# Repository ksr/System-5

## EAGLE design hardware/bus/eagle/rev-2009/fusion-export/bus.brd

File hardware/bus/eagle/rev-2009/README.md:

# Bus backplane, 2009 (from Eagle's backups)

Copied 2026-10-26 from `~/Documents/Projects/elf-2/ksrcad/Bus/`, where they sat beside the Rev A/B/C folders:
`eagle-backups/bus.b##` (board) and `bus.s##` (schematic), both dated 2009-02-04, Eagle 4 binary.
`bus.brd` and `bus.sch` are byte-identical copies under the names Eagle and Fusion open.

Exported from Fusion 2026-10-26 (`fusion-export/`) and converted: `hardware/bus/kicad/rev-2009/` (netlist proof MATCH
36/36), redrawn in `hardware/bus/kicad/rev-2009/schematic/`.

What the board is: **six 36-pin slots** (`C36A`), every pin bussed, 8 mounting holes, and X1, a 2-pin power connector.
Slot pins 1-30 are the System-5 bus pin for pin (pin 1 = +5V, named `5V` here; 30 = GND); 31-33 = -EF1, -EF2, -EF3
(silkscreened above the 30); 34-36 = -INP, -OUT, EXP (below). A 30-pin card fits the middle 30.
Against the 2005 Rev B board (`../rev-b/fab/bus-rev-b-silkscreen.png`): the same six 36-pin slots, but pin 36 is EXP
(Rev B: -IOM) and there is no regulator, LED or capacitors.
**X1 on the copper** (DRC of the conversion, 2026-10-26): the GND track runs down the board edge and ends on X1's pad 2, so X1 pin 2 IS GND (Eagle's netlist never logged it: the track was drawn onto the pad, not connected); both +5V branches dangle (a 75 mm run down the edge and a 7 mm stub ending about 9.5 mm from X1): X1 pin 1 is connected to nothing. X1 was evidently moved after routing. So X1 brings in GND only; +5V needs a wire from X1 pin 1 to the 5V track (slot pin 1) or comes in through a slot. To confirm with a meter: X1.2 to slot pin 30 beeps, X1.1 to slot pin 1 does not.
Photos of two bare boards (both sides): `photos/2026-10-26-*.jpg`. (The other names in the binary file, U4, DTPA, DN0..., are schematic leftovers, not parts on the board.)

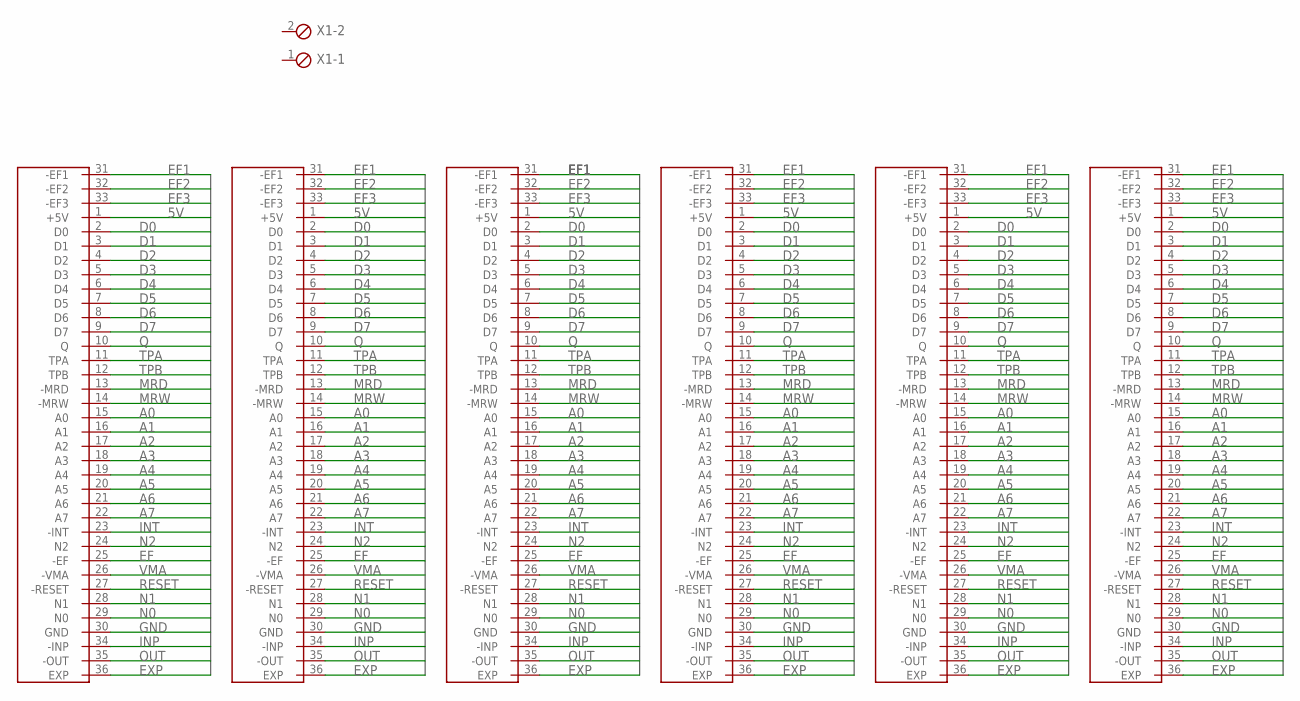
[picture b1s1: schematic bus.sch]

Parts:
U$1, U$2, U$3, U$4, U$5, U$6: C36A
X1: MPT2; 2POL254

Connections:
5V: U$1.1 (+5V), U$2.1 (+5V), U$3.1 (+5V), U$4.1 (+5V), U$5.1 (+5V), U$6.1 (+5V)
A0: U$1.15 (A0), U$2.15 (A0), U$3.15 (A0), U$4.15 (A0), U$5.15 (A0), U$6.15 (A0)
A1: U$1.16 (A1), U$2.16 (A1), U$3.16 (A1), U$4.16 (A1), U$5.16 (A1), U$6.16 (A1)
A2: U$1.17 (A2), U$2.17 (A2), U$3.17 (A2), U$4.17 (A2), U$5.17 (A2), U$6.17 (A2)
A3: U$1.18 (A3), U$2.18 (A3), U$3.18 (A3), U$4.18 (A3), U$5.18 (A3), U$6.18 (A3)
A4: U$1.19 (A4), U$2.19 (A4), U$3.19 (A4), U$4.19 (A4), U$5.19 (A4), U$6.19 (A4)
A5: U$1.20 (A5), U$2.20 (A5), U$3.20 (A5), U$4.20 (A5), U$5.20 (A5), U$6.20 (A5)
A6: U$1.21 (A6), U$2.21 (A6), U$3.21 (A6), U$4.21 (A6), U$5.21 (A6), U$6.21 (A6)
A7: U$1.22 (A7), U$2.22 (A7), U$3.22 (A7), U$4.22 (A7), U$5.22 (A7), U$6.22 (A7)
D0: U$1.2 (D0), U$2.2 (D0), U$3.2 (D0), U$4.2 (D0), U$5.2 (D0), U$6.2 (D0)
D1: U$1.3 (D1), U$2.3 (D1), U$3.3 (D1), U$4.3 (D1), U$5.3 (D1), U$6.3 (D1)
D2: U$1.4 (D2), U$2.4 (D2), U$3.4 (D2), U$4.4 (D2), U$5.4 (D2), U$6.4 (D2)
D3: U$1.5 (D3), U$2.5 (D3), U$3.5 (D3), U$4.5 (D3), U$5.5 (D3), U$6.5 (D3)
D4: U$1.6 (D4), U$2.6 (D4), U$3.6 (D4), U$4.6 (D4), U$5.6 (D4), U$6.6 (D4)
D5: U$1.7 (D5), U$2.7 (D5), U$3.7 (D5), U$4.7 (D5), U$5.7 (D5), U$6.7 (D5)
D6: U$1.8 (D6), U$2.8 (D6), U$3.8 (D6), U$4.8 (D6), U$5.8 (D6), U$6.8 (D6)
D7: U$1.9 (D7), U$2.9 (D7), U$3.9 (D7), U$4.9 (D7), U$5.9 (D7), U$6.9 (D7)
EF: U$1.25 (-EF), U$2.25 (-EF), U$3.25 (-EF), U$4.25 (-EF), U$5.25 (-EF), U$6.25 (-EF)
EF1: U$1.31 (-EF1), U$2.31 (-EF1), U$3.31 (-EF1), U$4.31 (-EF1), U$5.31 (-EF1), U$6.31 (-EF1)
EF2: U$1.32 (-EF2), U$2.32 (-EF2), U$3.32 (-EF2), U$4.32 (-EF2), U$5.32 (-EF2), U$6.32 (-EF2)
EF3: U$1.33 (-EF3), U$2.33 (-EF3), U$3.33 (-EF3), U$4.33 (-EF3), U$5.33 (-EF3), U$6.33 (-EF3)
EXP: U$1.36 (EXP), U$2.36 (EXP), U$3.36 (EXP), U$4.36 (EXP), U$5.36 (EXP), U$6.36 (EXP)
GND: U$1.30 (GND), U$2.30 (GND), U$3.30 (GND), U$4.30 (GND), U$5.30 (GND), U$6.30 (GND)
INP: U$1.34 (-INP), U$2.34 (-INP), U$3.34 (-INP), U$4.34 (-INP), U$5.34 (-INP), U$6.34 (-INP)
INT: U$1.23 (-INT), U$2.23 (-INT), U$3.23 (-INT), U$4.23 (-INT), U$5.23 (-INT), U$6.23 (-INT)
MRD: U$1.13 (-MRD), U$2.13 (-MRD), U$3.13 (-MRD), U$4.13 (-MRD), U$5.13 (-MRD), U$6.13 (-MRD)
MRW: U$1.14 (-MRW), U$2.14 (-MRW), U$3.14 (-MRW), U$4.14 (-MRW), U$5.14 (-MRW), U$6.14 (-MRW)
N0: U$1.29 (N0), U$2.29 (N0), U$3.29 (N0), U$4.29 (N0), U$5.29 (N0), U$6.29 (N0)
N1: U$1.28 (N1), U$2.28 (N1), U$3.28 (N1), U$4.28 (N1), U$5.28 (N1), U$6.28 (N1)
N2: U$1.24 (N2), U$2.24 (N2), U$3.24 (N2), U$4.24 (N2), U$5.24 (N2), U$6.24 (N2)
OUT: U$1.35 (-OUT), U$2.35 (-OUT), U$3.35 (-OUT), U$4.35 (-OUT), U$5.35 (-OUT), U$6.35 (-OUT)
Q: U$1.10 (Q), U$2.10 (Q), U$3.10 (Q), U$4.10 (Q), U$5.10 (Q), U$6.10 (Q)
RESET: U$1.27 (-RESET), U$2.27 (-RESET), U$3.27 (-RESET), U$4.27 (-RESET), U$5.27 (-RESET), U$6.27 (-RESET)
TPA: U$1.11 (TPA), U$2.11 (TPA), U$3.11 (TPA), U$4.11 (TPA), U$5.11 (TPA), U$6.11 (TPA)
TPB: U$1.12 (TPB), U$2.12 (TPB), U$3.12 (TPB), U$4.12 (TPB), U$5.12 (TPB), U$6.12 (TPB)
VMA: U$1.26 (-VMA), U$2.26 (-VMA), U$3.26 (-VMA), U$4.26 (-VMA), U$5.26 (-VMA), U$6.26 (-VMA)

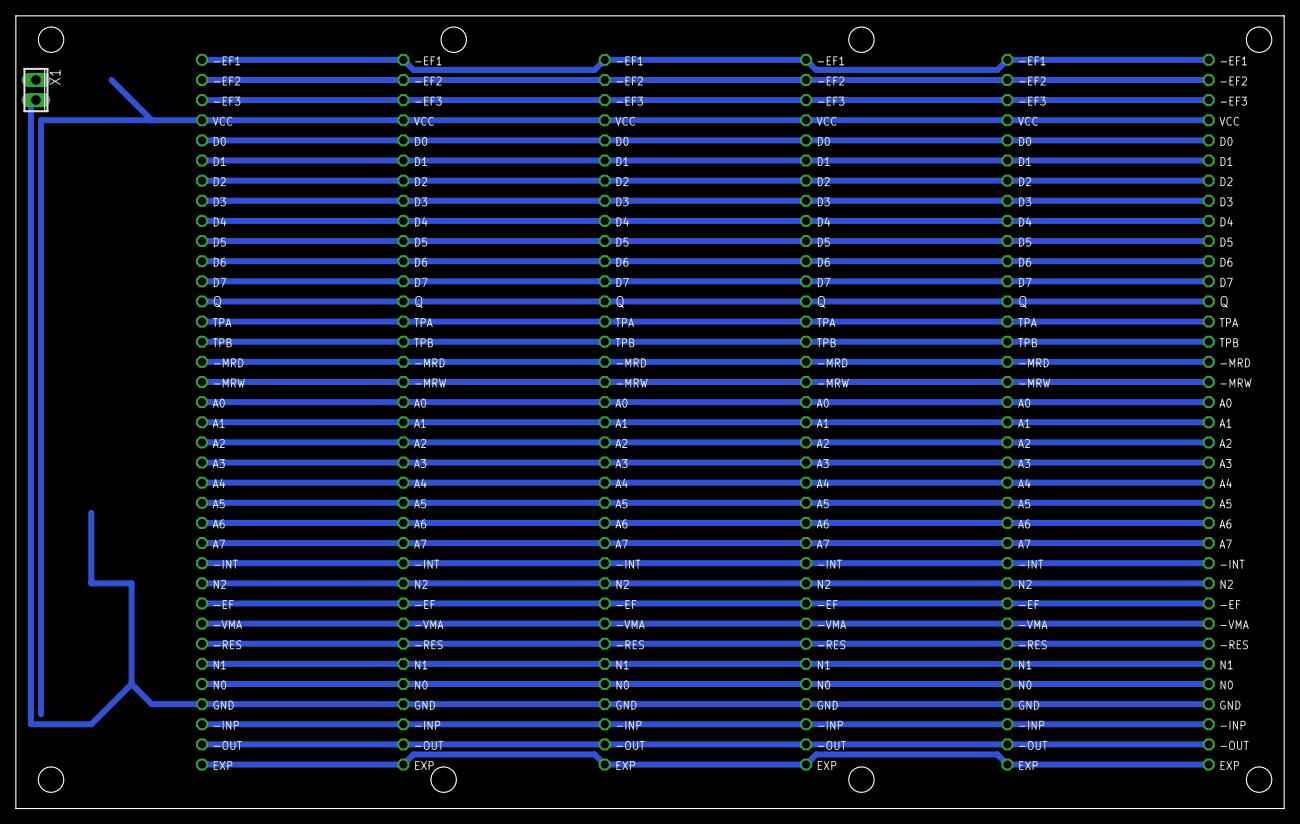
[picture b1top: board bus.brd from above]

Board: 2 copper layers, 160.0 x 100.0 mm, 7 parts (0 on the bottom side), 36 nets.

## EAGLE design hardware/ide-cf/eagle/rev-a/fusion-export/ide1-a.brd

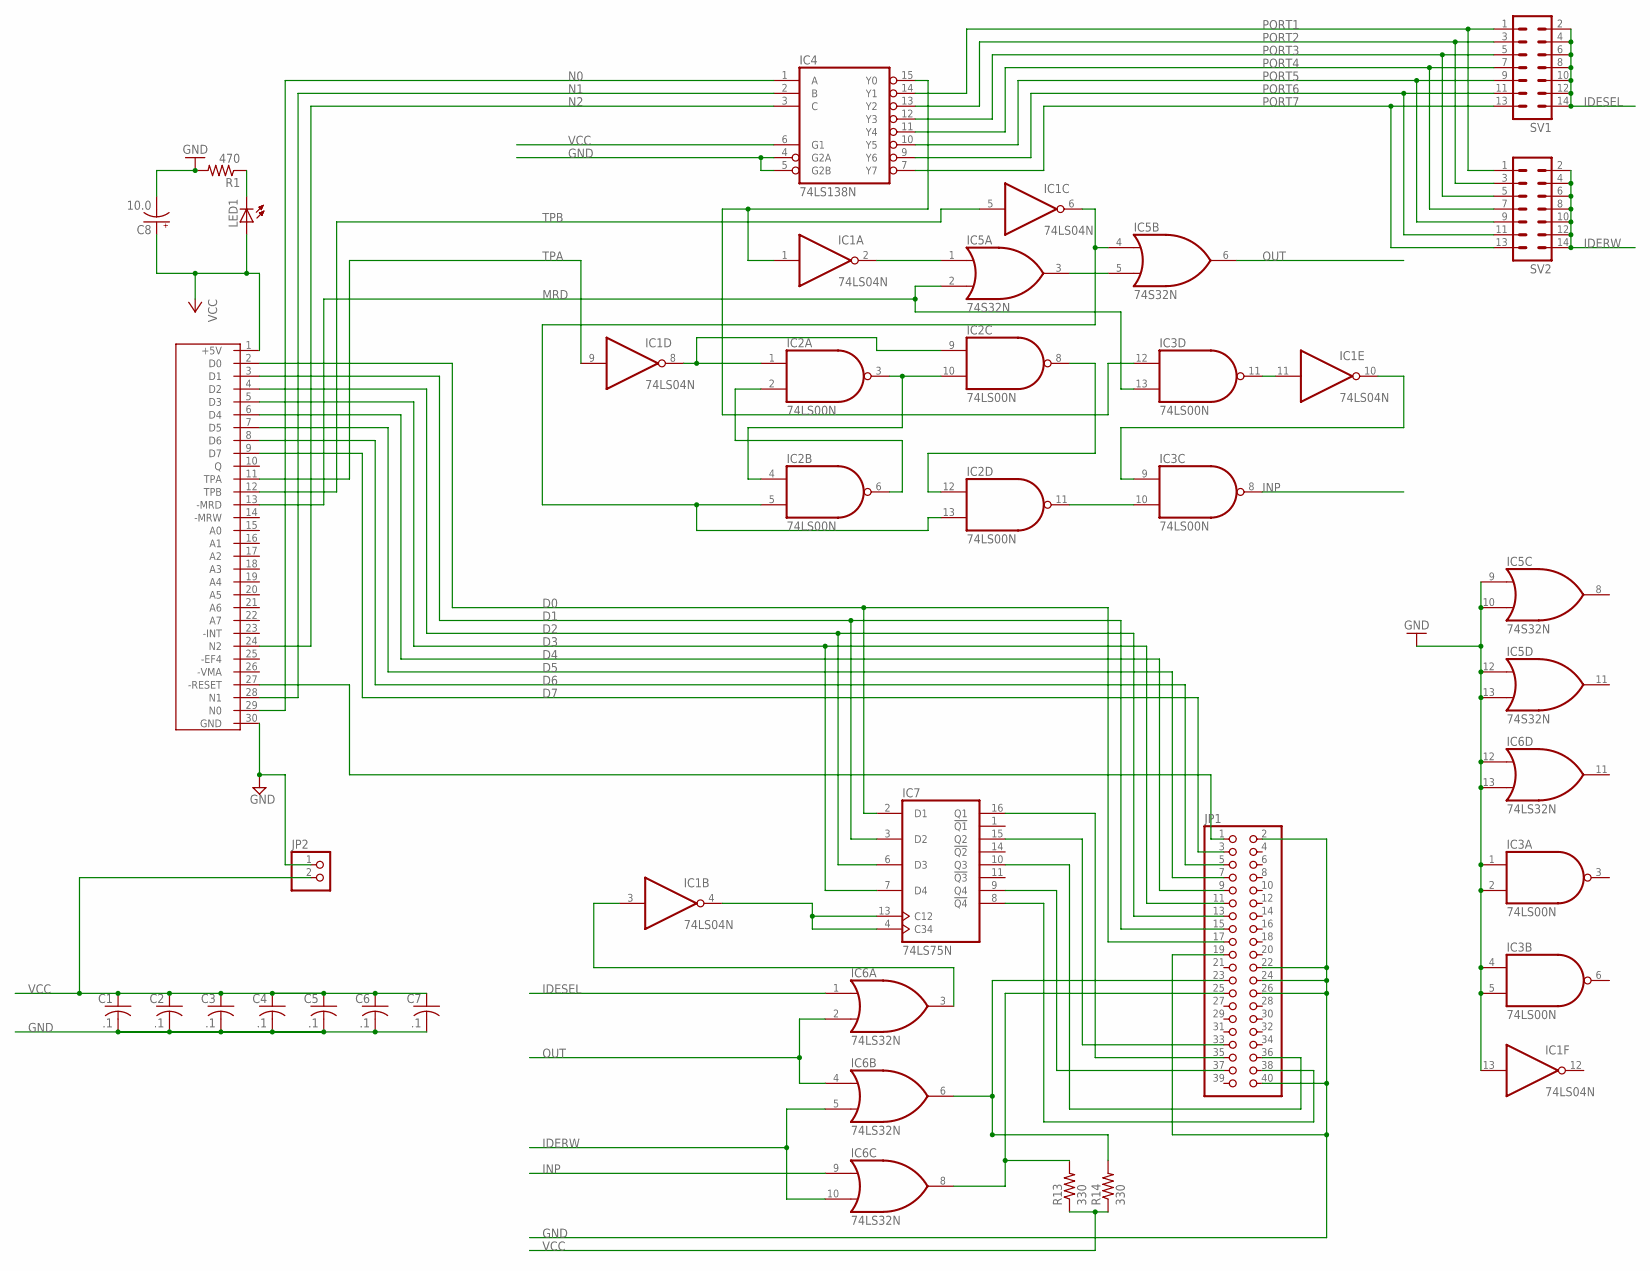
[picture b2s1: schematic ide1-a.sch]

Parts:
C1, C2, C3, C4, C5, C6, C7: .1; C025-050X050
C8: 10.0; E2,5-7
IC1: 74LS04N; DIL14
IC2, IC3: 74LS00N; DIL14
IC4: 74LS138N; DIL16
IC5: 74S32N; DIL14
IC6: 74LS32N; DIL14
IC7: 74LS75N; DIL16
JP1: PINHD-2X20; 2X20
JP2: PINHD-1X2; 1X02
LED1: LED5MM
R1: 470; 0207/7
R13, R14: 330; 0207/7
SV1, SV2: MA07-2
U$1: C30

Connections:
D0: IC7.2 (D1), JP1.17, U$1.2 (D0)
D1: IC7.3 (D2), JP1.15, U$1.3 (D1)
D2: IC7.6 (D3), JP1.13, U$1.4 (D2)
D3: IC7.7 (D4), JP1.11, U$1.5 (D3)
D4: JP1.9, U$1.6 (D4)
D5: JP1.7, U$1.7 (D5)
D6: JP1.5, U$1.8 (D6)
D7: JP1.3, U$1.9 (D7)
GND: C1.2, C2.2, C3.2, C4.2, C5.2, C6.2, C7.2, C8.-, IC1.7 (GND), IC1.13 (I), IC2.7 (GND), IC3.1 (I0), IC3.2 (I1), IC3.4 (I0), IC3.5 (I1), IC3.7 (GND), IC4.4 (G2A), IC4.5 (G2B), IC4.8 (GND), IC5.7 (GND), IC5.9 (I0), IC5.10 (I1), IC5.12 (I0), IC5.13 (I1), IC6.7 (GND), IC6.12 (I0), IC6.13 (I1), IC7.12 (GND), JP1.2, JP1.19, JP1.22, JP1.24, JP1.26, JP1.40, JP2.1, R1.2, U$1.30 (GND)
IDERW: IC6.5 (I1), IC6.10 (I1), SV2.2, SV2.4, SV2.6, SV2.8, SV2.10, SV2.12, SV2.14
IDESEL: IC6.1 (I0), SV1.2, SV1.4, SV1.6, SV1.8, SV1.10, SV1.12, SV1.14
INP: IC3.8 (O), IC6.9 (I0)
MRD: IC3.13 (I1), IC5.2 (I1), U$1.13 (-MRD)
N0: IC4.1 (A), U$1.29 (N0)
N1: IC4.2 (B), U$1.28 (N1)
N2: IC4.3 (C), U$1.24 (N2)
unnamed: IC1.1 (I), IC3.12 (I0), IC4.15 (Y0)
unnamed: IC1.2 (O), IC5.1 (I0)
unnamed: IC2.3 (O), IC2.4 (I0), IC2.10 (I1)
unnamed: IC5.3 (O), IC5.5 (I1)
unnamed: IC1.6 (O), IC2.5 (I1), IC2.13 (I1), IC5.4 (I0)
unnamed: IC2.2 (I1), IC2.6 (O)
unnamed: IC1.8 (O), IC2.1 (I0), IC2.9 (I0)
unnamed: IC1.10 (O), IC3.9 (I0)
unnamed: IC2.8 (O), IC2.12 (I0)
unnamed: IC1.3 (I), IC6.3 (O)
unnamed: IC2.11 (O), IC3.10 (I1)
unnamed: IC1.11 (I), IC3.11 (O)
unnamed: LED1.K (C), R1.1
unnamed: IC1.4 (O), IC7.4 (C34), IC7.13 (C12)
unnamed: IC7.16 (Q1), JP1.35
unnamed: IC7.15 (Q2), JP1.33
unnamed: IC7.10 (Q3), JP1.36
unnamed: IC7.9 (Q4), JP1.37
unnamed: IC7.8 (!Q4), JP1.38
unnamed: IC6.6 (O), JP1.23, R14.2
unnamed: IC6.8 (O), JP1.25, R13.2
OUT: IC5.6 (O), IC6.2 (I1), IC6.4 (I0)
PORT1: IC4.14 (Y1), SV1.1, SV2.1
PORT2: IC4.13 (Y2), SV1.3, SV2.3
PORT3: IC4.12 (Y3), SV1.5, SV2.5
PORT4: IC4.11 (Y4), SV1.7, SV2.7
PORT5: IC4.10 (Y5), SV1.9, SV2.9
PORT6: IC4.9 (Y6), SV1.11, SV2.11
PORT7: IC4.7 (Y7), SV1.13, SV2.13
RESET: JP1.1, U$1.27 (-RESET)
TPA: IC1.9 (I), U$1.11 (TPA)
TPB: IC1.5 (I), U$1.12 (TPB)
VCC: C1.1, C2.1, C3.1, C4.1, C5.1, C6.1, C7.1, C8.+, IC1.14 (VCC), IC2.14 (VCC), IC3.14 (VCC), IC4.6 (G1), IC4.16 (VCC), IC5.14 (VCC), IC6.14 (VCC), IC7.5 (VCC), JP2.2, LED1.A, R13.1, R14.1, U$1.1 (+5V)

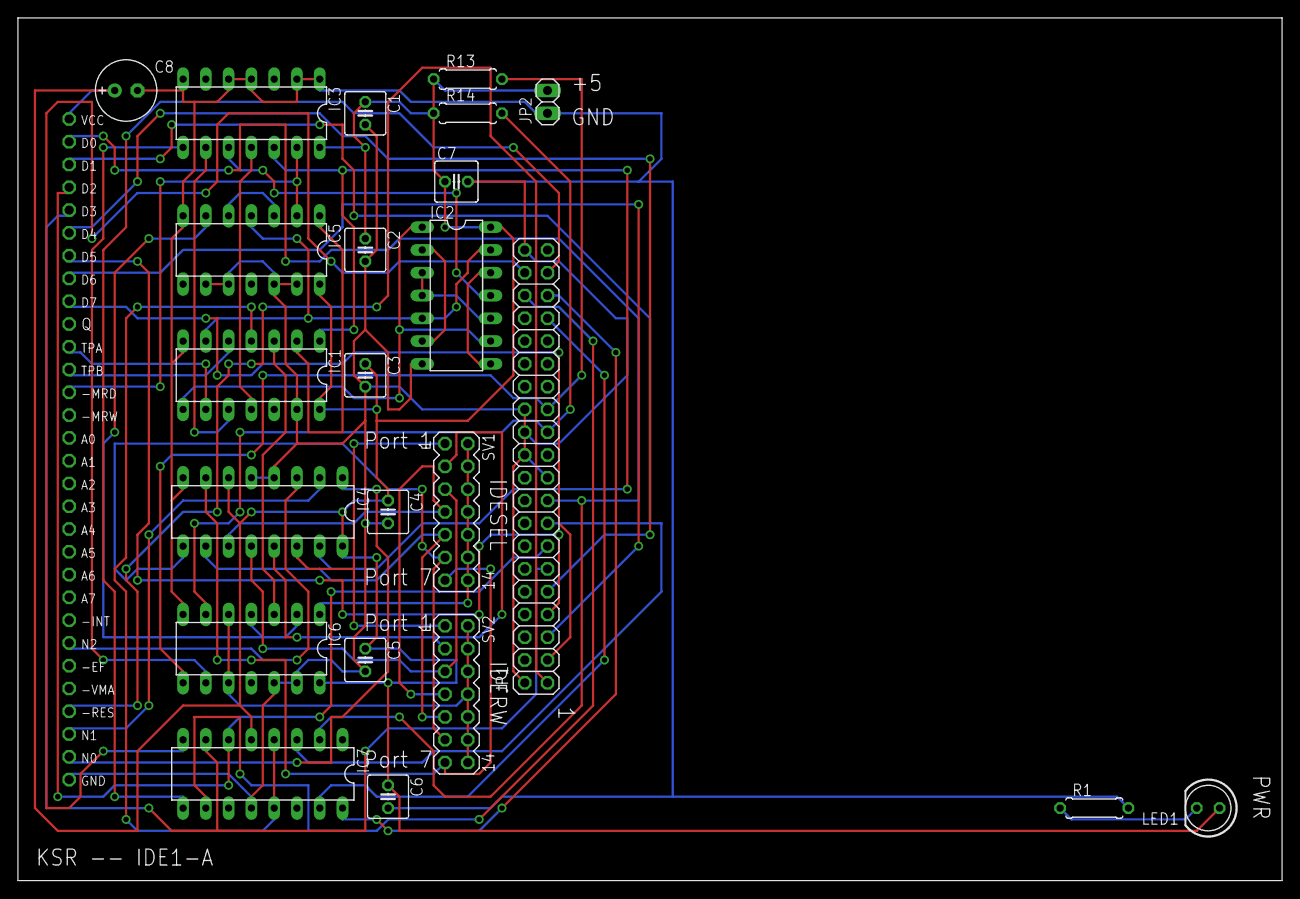
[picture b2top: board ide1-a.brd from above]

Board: 2 copper layers, 140.9 x 96.2 mm, 24 parts (0 on the bottom side), 49 nets.

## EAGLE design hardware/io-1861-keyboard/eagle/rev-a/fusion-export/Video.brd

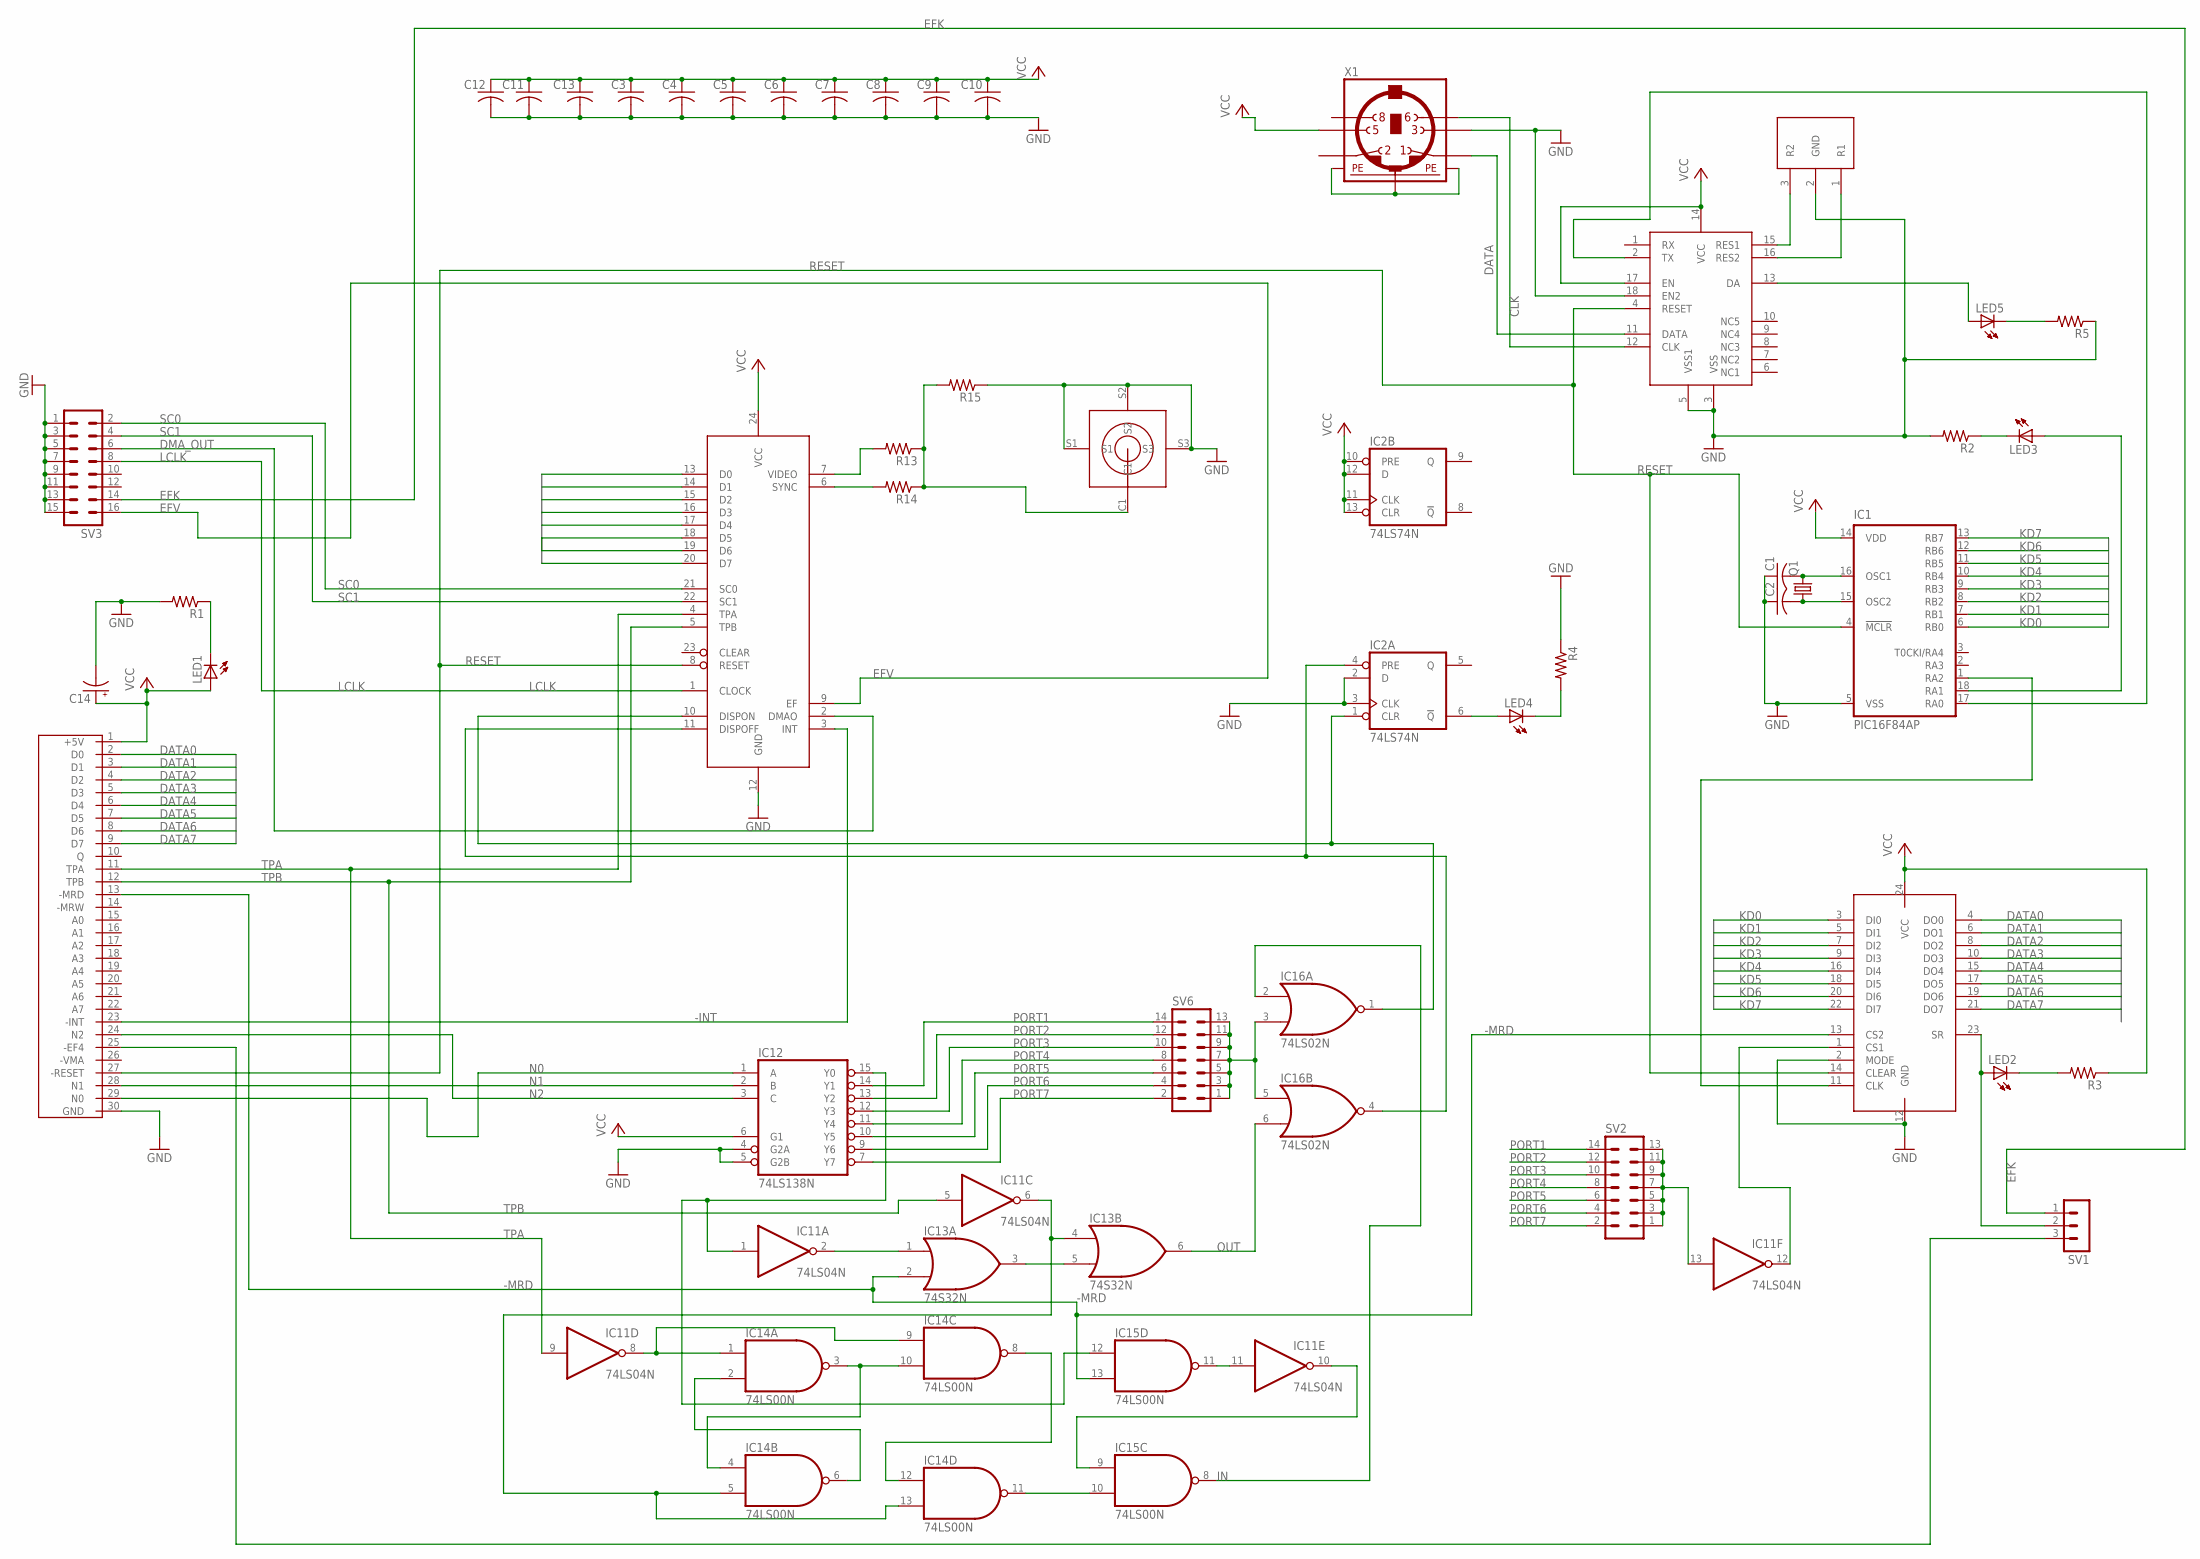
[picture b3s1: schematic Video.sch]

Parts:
C1, C2: C-US025-024X044; C025-024X044
C3, C4, C5, C6, C7, C8, C9, C10, C11, C12, C13: C-US025-050X050; C025-050X050
C14: CPOL-USE2.5-7; E2,5-7
IC1: PIC16F84AP; DIL18
IC2: 74LS74N; DIL14
IC11: 74LS04N; DIL14
IC12: 74LS138N; DIL16
IC13: 74S32N; DIL14
IC14, IC15: 74LS00N; DIL14
IC16: 74LS02N; DIL14
LED1, LED2, LED3, LED4, LED5: LED5MM
Q1: CRYTALHC49U-V; HC49U-V
R1, R2, R3, R4, R5, R13, R14, R15: R-US_0207/2V; 0207/2V
SV1: MA03-1
SV2, SV6: MA07-2
SV3: MA08-2
U$1: 1852; DIL24
U$2: C30
U$3: CDP1861; DIP24
U$4: RCA
U$5: PAKVI; DIL18
U$6: RESONATOR; MA03-1
X1: MINI_DIN_6; M_DIN6

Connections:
-INT: U$2.23 (-INT), U$3.3 (INT)
-MRD: IC13.2 (I1), IC15.13 (I1), U$1.13 (CS2), U$2.13 (-MRD)
CLK: U$5.12 (CLK), X1.6
DATA: U$5.11 (DATA), X1.1
DATA0: U$1.4 (DO0), U$2.2 (D0), U$3.13 (D0)
DATA1: U$1.6 (DO1), U$2.3 (D1), U$3.14 (D1)
DATA2: U$1.8 (DO2), U$2.4 (D2), U$3.15 (D2)
DATA3: U$1.10 (DO3), U$2.5 (D3), U$3.16 (D3)
DATA4: U$1.15 (DO4), U$2.6 (D4), U$3.17 (D4)
DATA5: U$1.17 (DO5), U$2.7 (D5), U$3.18 (D5)
DATA6: U$1.19 (DO6), U$2.8 (D6), U$3.19 (D6)
DATA7: U$1.21 (DO7), U$2.9 (D7), U$3.20 (D7)
DMA_OUT: SV3.6, U$3.2 (DMAO)
EFK: SV1.1, SV3.14
EFV: SV3.16, U$3.9 (EF)
GND: C1.1, C2.1, C3.2, C4.2, C5.2, C6.2, C7.2, C8.2, C9.2, C10.2, C11.2, C12.2, C13.2, C14.-, IC1.5 (VSS), IC2.2 (D), IC2.3 (CLK), IC2.7 (GND), IC11.7 (GND), IC12.4 (G2A), IC12.5 (G2B), IC12.8 (GND), IC13.7 (GND), IC14.7 (GND), IC15.7 (GND), IC16.7 (GND), R1.2, R2.2, R4.1, R5.1, R15.1, SV3.1, SV3.3, SV3.5, SV3.7, SV3.9, SV3.11, SV3.13, SV3.15, U$1.2 (MODE), U$1.12 (GND), U$2.30 (GND), U$3.12 (GND), U$4.S1, U$4.S2, U$4.S3, U$5.3 (VSS), U$5.5 (VSS1), U$5.18 (EN2), U$6.2 (GND), X1.3
IN: IC15.8 (O), IC16.2 (I0)
KD0: IC1.6 (RB0), U$1.3 (DI0)
KD1: IC1.7 (RB1), U$1.5 (DI1)
KD2: IC1.8 (RB2), U$1.7 (DI2)
KD3: IC1.9 (RB3), U$1.9 (DI3)
KD4: IC1.10 (RB4), U$1.16 (DI4)
KD5: IC1.11 (RB5), U$1.18 (DI5)
KD6: IC1.12 (RB6), U$1.20 (DI6)
KD7: IC1.13 (RB7), U$1.22 (DI7)
LCLK: SV3.8, U$3.1 (CLOCK)
N0: IC12.1 (A), U$2.29 (N0)
N1: IC12.2 (B), U$2.28 (N1)
N2: IC12.3 (C), U$2.24 (N2)
unnamed: U$5.15 (RES1), U$6.3 (R2)
unnamed: U$5.16 (RES2), U$6.1 (R1)
unnamed: IC1.17 (RA0), U$5.2 (TX)
unnamed: LED3.K (C), R2.1
unnamed: IC11.1 (I), IC12.15 (Y0), IC15.12 (I0)
unnamed: IC1.18 (RA1), LED3.A
unnamed: R14.2, U$3.6 (SYNC)
unnamed: R13.2, U$3.7 (VIDEO)
unnamed: R13.1, R14.1, R15.2, U$4.C1
unnamed: IC11.2 (O), IC13.1 (I0)
unnamed: IC13.3 (O), IC13.5 (I1)
unnamed: IC14.3 (O), IC14.4 (I0), IC14.10 (I1)
unnamed: IC14.2 (I1), IC14.6 (O)
unnamed: IC11.8 (O), IC14.1 (I0), IC14.9 (I0)
unnamed: IC1.1 (RA2), U$1.11 (CLK)
unnamed: LED2.A, SV1.2, U$1.23 (SR)
unnamed: SV1.3, U$2.25 (-EF4)
unnamed: IC11.12 (O), U$1.1 (CS1)
unnamed: C1.2, IC1.16 (OSC1), Q1.2
unnamed: IC11.13 (I), SV2.1, SV2.3, SV2.5, SV2.7, SV2.9, SV2.11, SV2.13
unnamed: C2.2, IC1.15 (OSC2), Q1.1
unnamed: LED1.K (C), R1.1
unnamed: LED2.K (C), R3.2
unnamed: IC2.6 (!Q), LED4.A
unnamed: LED4.K (C), R4.2
unnamed: IC14.8 (O), IC14.12 (I0)
unnamed: LED5.A, U$5.13 (DA)
unnamed: IC11.6 (O), IC13.4 (I0), IC14.5 (I1), IC14.13 (I1)
unnamed: LED5.K (C), R5.2
unnamed: X1.SH1 (PE1), X1.SH2 (PE2), X1.SH3 (PE3)
unnamed: IC14.11 (O), IC15.10 (I1)
unnamed: IC11.10 (O), IC15.9 (I0)
unnamed: IC11.11 (I), IC15.11 (O)
unnamed: IC16.3 (I1), IC16.5 (I0), SV6.1, SV6.3, SV6.5, SV6.7, SV6.9, SV6.11, SV6.13
unnamed: IC2.1 (CLR), IC16.1 (O), U$3.10 (DISPON)
unnamed: IC2.4 (PRE), IC16.4 (O), U$3.11 (DISPOFF)
OUT: IC13.6 (O), IC16.6 (I1)
PORT1: IC12.14 (Y1), SV2.14, SV6.14
PORT2: IC12.13 (Y2), SV2.12, SV6.12
PORT3: IC12.12 (Y3), SV2.10, SV6.10
PORT4: IC12.11 (Y4), SV2.8, SV6.8
PORT5: IC12.10 (Y5), SV2.6, SV6.6
PORT6: IC12.9 (Y6), SV2.4, SV6.4
PORT7: IC12.7 (Y7), SV2.2, SV6.2
RESET: IC1.4 (!MCLR), U$1.14 (CLEAR), U$2.27 (-RESET), U$3.8 (RESET), U$5.4 (RESET)
SC0: SV3.2, U$3.21 (SC0)
SC1: SV3.4, U$3.22 (SC1)
TPA: IC11.9 (I), U$2.11 (TPA), U$3.4 (TPA)
TPB: IC11.5 (I), U$2.12 (TPB), U$3.5 (TPB)
VCC: C3.1, C4.1, C5.1, C6.1, C7.1, C8.1, C9.1, C10.1, C11.1, C12.1, C13.1, C14.+, IC1.14 (VDD), IC2.10 (PRE), IC2.11 (CLK), IC2.12 (D), IC2.13 (CLR), IC2.14 (VCC), IC11.14 (VCC), IC12.6 (G1), IC12.16 (VCC), IC13.14 (VCC), IC14.14 (VCC), IC15.14 (VCC), IC16.14 (VCC), LED1.A, R3.1, U$1.24 (VCC), U$2.1 (+5V), U$3.24 (VCC), U$5.14 (VCC), U$5.17 (EN), X1.5

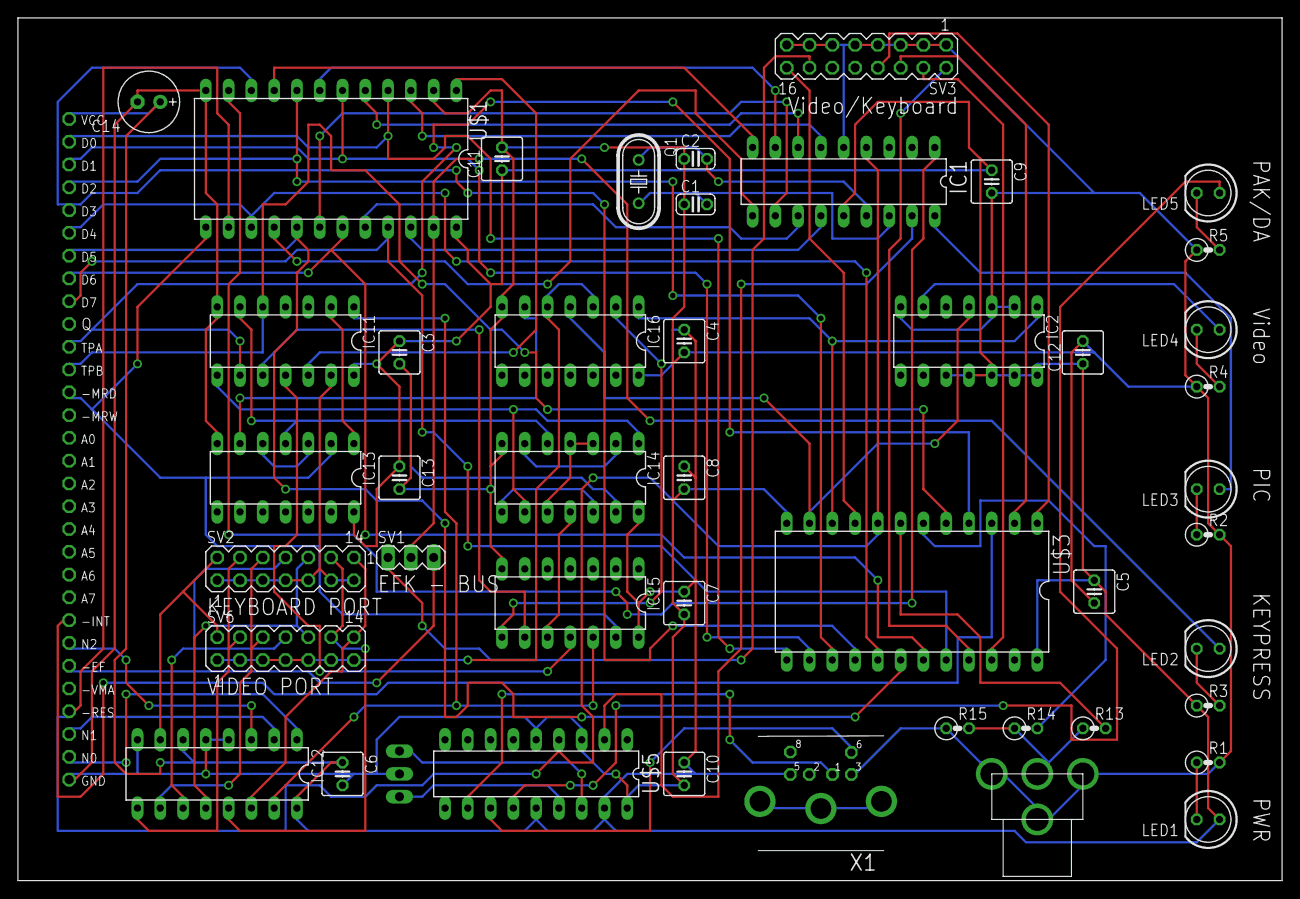
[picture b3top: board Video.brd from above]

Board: 2 copper layers, 140.9 x 96.2 mm, 47 parts (0 on the bottom side), 79 nets.
